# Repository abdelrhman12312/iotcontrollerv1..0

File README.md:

# iotcontrollerv1..0
I made a esp8266 controller board that can control up to 
16 relays with the MCP23017 with kicad

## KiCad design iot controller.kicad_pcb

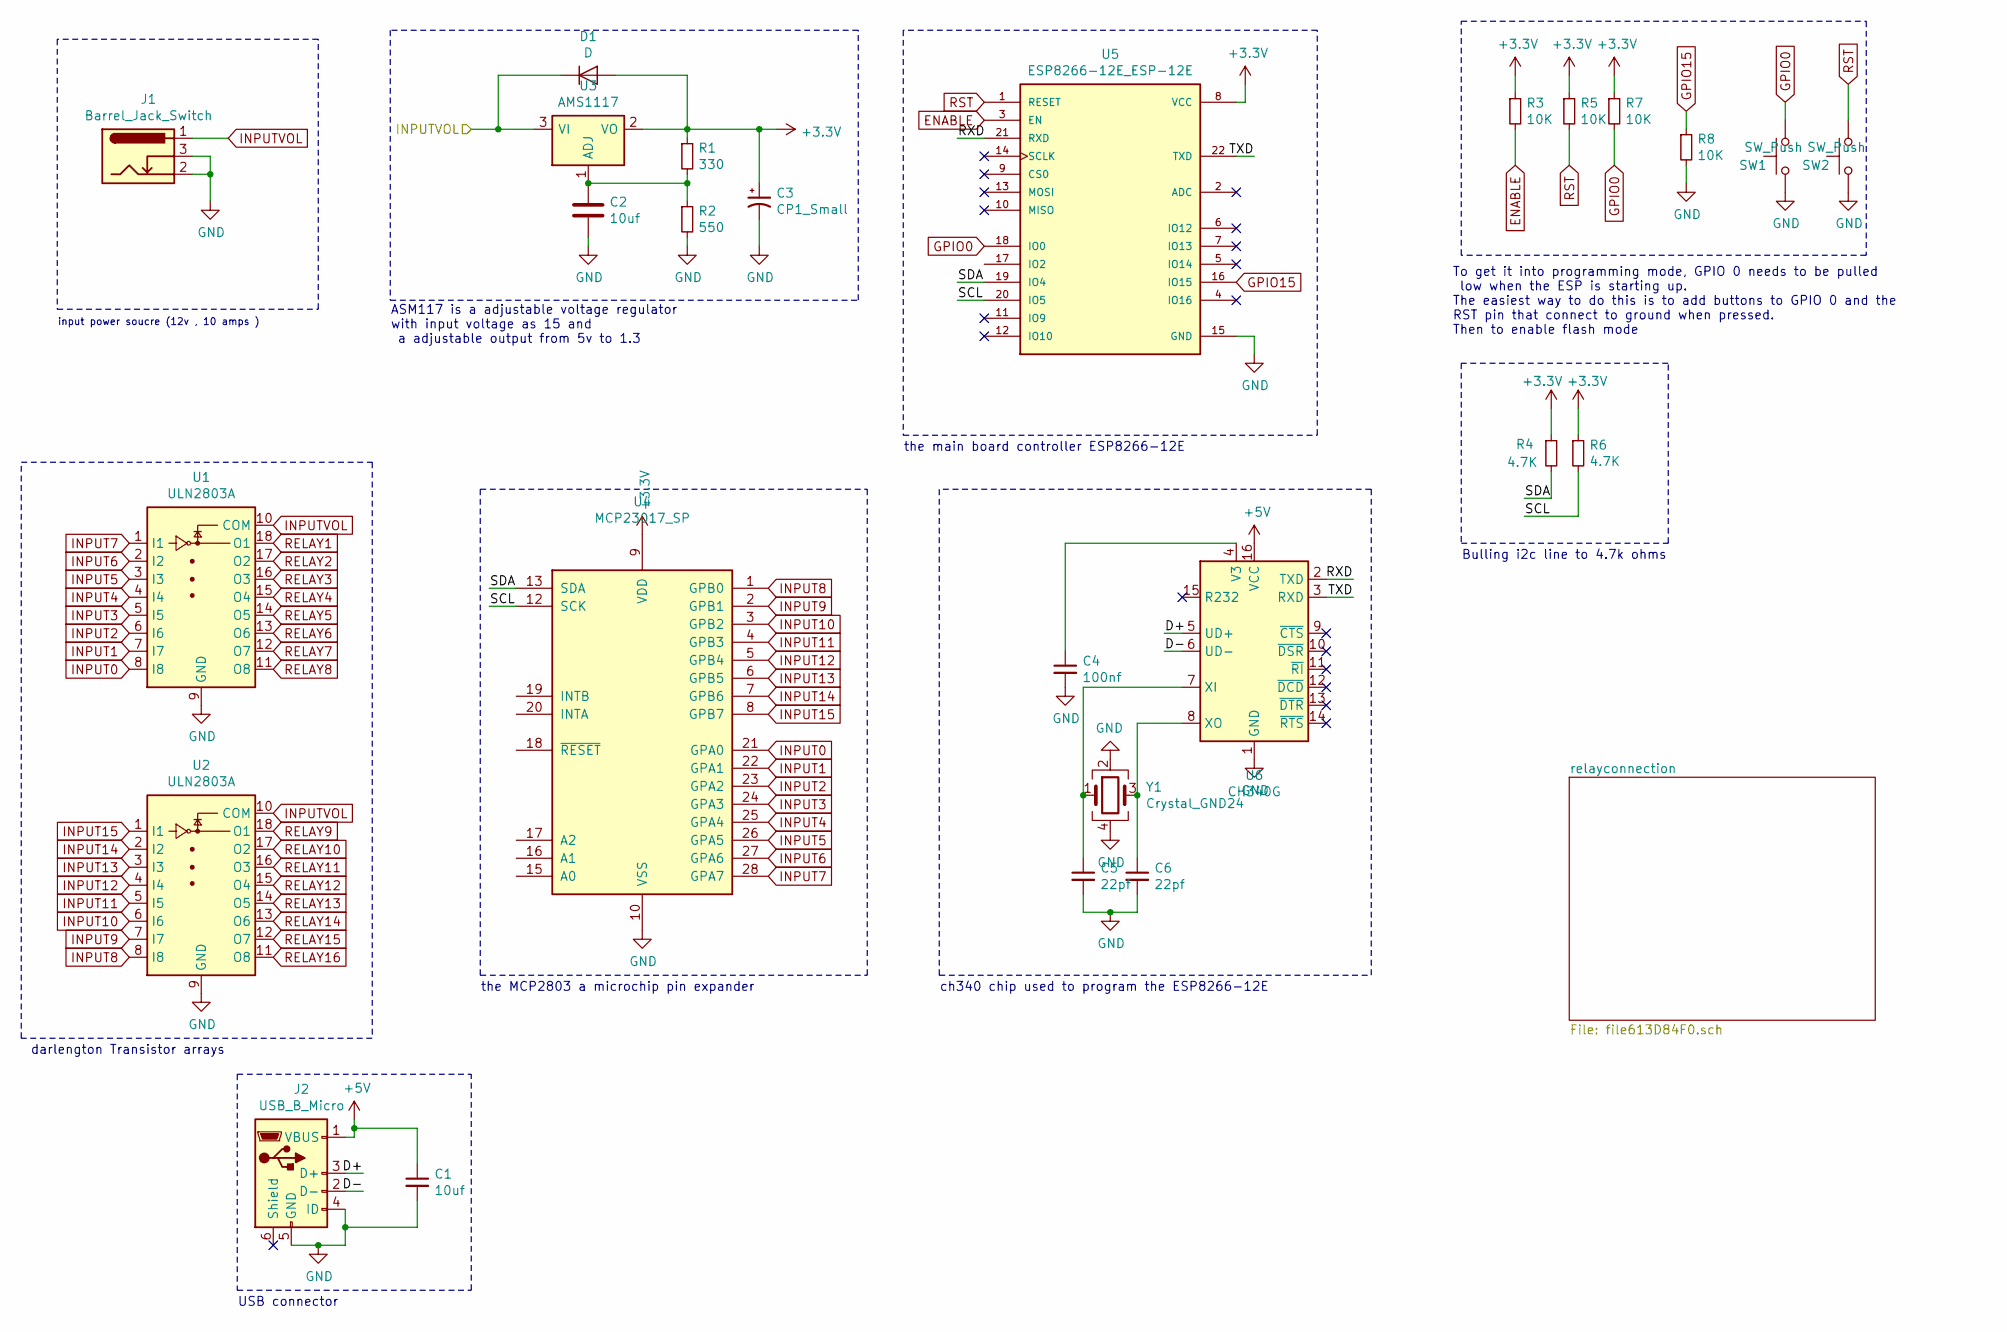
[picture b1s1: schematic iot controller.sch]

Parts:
C1, C2: 10uf; C_0603_1608Metric_Pad1.05x0.95mm_HandSolder
C3: CP1_Small; CP_Radial_D18.0mm_P7.50mm
C4: 100nf; C_0805_2012Metric_Pad1.15x1.40mm_HandSolder
C5, C6: 22pf; C_0805_2012Metric_Pad1.15x1.40mm_HandSolder
D1: D; D_SOD-123
J1: Barrel_Jack_Switch; BarrelJack_Horizontal
J2: USB_B_Micro; USB_Micro-B_GCT_USB3076-30-A
R1: 330; R_0805_2012Metric_Pad1.15x1.40mm_HandSolder
R2: 550; R_0805_2012Metric_Pad1.15x1.40mm_HandSolder
R3, R5, R7, R8: 10K; R_0805_2012Metric_Pad1.15x1.40mm_HandSolder
R4, R6: 4.7K; R_0805_2012Metric_Pad1.15x1.40mm_HandSolder
SW1, SW2: SW_Push; SW_Push_SPST_NO_Alps_SKRK
U1, U2: ULN2803A; DIP-18_W7.62mm
U3: AMS1117; SOT-223-3_TabPin2
U4: MCP23017_SP; DIP-28_W7.62mm
U5: ESP8266-12E_ESP-12E; ESP-12E
U6: CH340G; SOIC-16_3.9x9.9mm_P1.27mm
Y1: Crystal_GND24; Crystal_SMD_SeikoEpson_FA238V-4Pin_3.2x2.5mm

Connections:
+3V3: C3.1, D1.2 (A), R1.1, R3.1, R4.1, R5.1, R6.1, R7.1, U3.2 (VO), U4.9 (VDD), U5.8 (VCC)
+5V: C1.1, J2.1 (VBUS), U6.16 (VCC)
/D+: J2.3 (D+), U6.5 (UD+)
/D-: J2.2 (D-), U6.6 (UD-)
/RXD: U5.21 (RXD), U6.2 (TXD)
/SCL: R6.2, U4.12 (SCK), U5.20 (IO5)
/SDA: R4.2, U4.13 (SDA), U5.19 (IO4)
/TXD: U5.22 (TXD), U6.3 (RXD)
ENABLE: R3.2, U5.3 (EN)
GND: C1.2, C2.2, C3.2, C4.2, C5.2, C6.2, J1.2, J1.3, J2.4 (ID), J2.5 (GND), R2.2, R8.2, SW1.1, SW2.1, U1.9 (GND), U2.9 (GND), U4.10 (VSS), U5.15 (GND), U6.1 (GND), Y1.2, Y1.4
GPIO0: R7.2, SW1.2, U5.18 (IO0)
GPIO15: R8.1, U5.16 (IO15)
INPUT0: U1.8 (I8), U4.21 (GPA0)
INPUT1: U1.7 (I7), U4.22 (GPA1)
INPUT2: U1.6 (I6), U4.23 (GPA2)
INPUT3: U1.5 (I5), U4.24 (GPA3)
INPUT4: U1.4 (I4), U4.25 (GPA4)
INPUT5: U1.3 (I3), U4.26 (GPA5)
INPUT6: U1.2 (I2), U4.27 (GPA6)
INPUT7: U1.1 (I1), U4.28 (GPA7)
INPUT8: U2.8 (I8), U4.1 (GPB0)
INPUT9: U2.7 (I7), U4.2 (GPB1)
INPUT10: U2.6 (I6), U4.3 (GPB2)
INPUT11: U2.5 (I5), U4.4 (GPB3)
INPUT12: U2.4 (I4), U4.5 (GPB4)
INPUT13: U2.3 (I3), U4.6 (GPB5)
INPUT14: U2.2 (I2), U4.7 (GPB6)
INPUT15: U2.1 (I1), U4.8 (GPB7)
INPUTVOL: D1.1 (K), J1.1, U1.10 (COM), U2.10 (COM), U3.3 (VI); also elsewhere on the board
unnamed: C2.1, R1.2, R2.1, U3.1 (ADJ)
unnamed: C4.1, U6.4 (V3)
unnamed: C5.1, U6.7 (XI), Y1.1
unnamed: C6.1, U6.8 (XO), Y1.3
RELAY1: U1.18 (O1); also elsewhere on the board
RELAY2: U1.17 (O2); also elsewhere on the board
RELAY3: U1.16 (O3); also elsewhere on the board
RELAY4: U1.15 (O4); also elsewhere on the board
RELAY5: U1.14 (O5); also elsewhere on the board
RELAY6: U1.13 (O6); also elsewhere on the board
RELAY7: U1.12 (O7); also elsewhere on the board
RELAY8: U1.11 (O8); also elsewhere on the board
RELAY9: U2.18 (O1); also elsewhere on the board
RELAY10: U2.17 (O2); also elsewhere on the board
RELAY11: U2.16 (O3); also elsewhere on the board
RELAY12: U2.15 (O4); also elsewhere on the board
RELAY13: U2.14 (O5); also elsewhere on the board
RELAY14: U2.13 (O6); also elsewhere on the board
RELAY15: U2.12 (O7); also elsewhere on the board
RELAY16: U2.11 (O8); also elsewhere on the board
RST: R5.2, SW2.2, U5.1 (RESET)

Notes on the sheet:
To get it into programming mode, GPIO 0 needs to be pulled low when the ESP is starting up. The easiest way to do this is to add buttons to GPIO 0 and the RST pin that connect to ground when pressed. Then to enable flash mode
Bulling i2c line to 4.7k ohms
input power soucre (12v , 10 amps )
ASM117 is a adjustable voltage regulator with input voltage as 15 and a adjustable output from 5v to 1.3
the main board controller ESP8266-12E
the MCP2803 a microchip pin expander
darlengton Transistor arrays
USB connector
ch340 chip used to program the ESP8266-12E

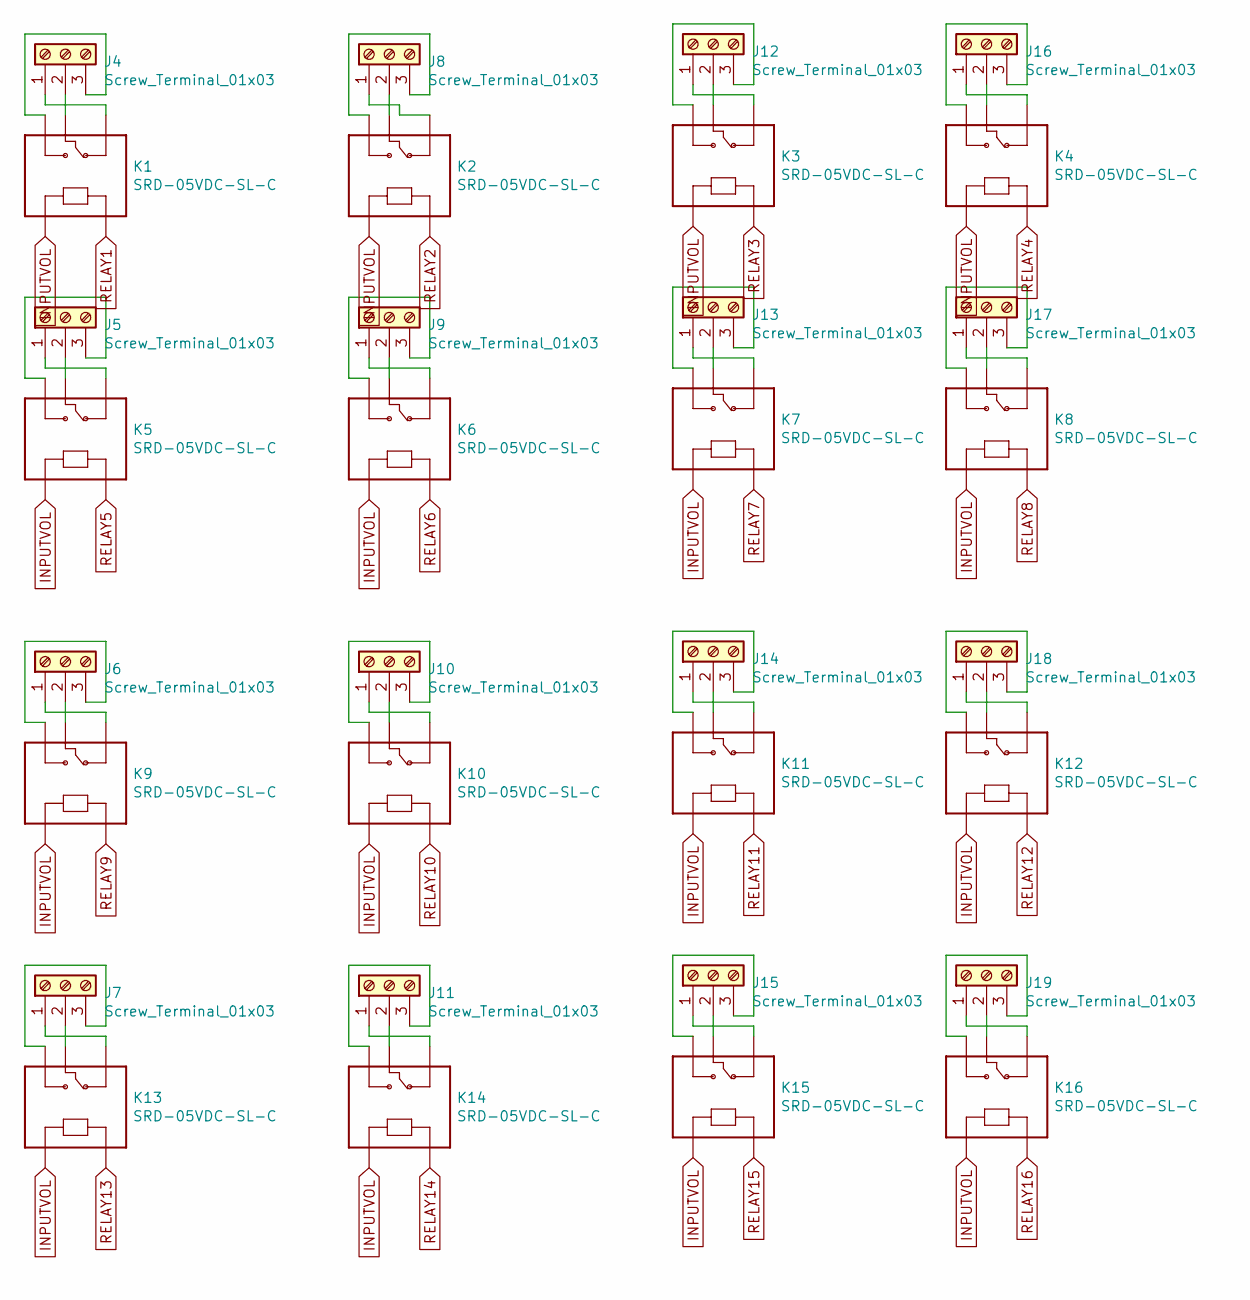
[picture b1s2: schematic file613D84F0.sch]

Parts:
J4, J5, J6, J7, J8, J9, J10, J11, J12, J13, J14, J15, J16, J17, J18, J19: Screw_Terminal_01x03; TerminalBlock_4Ucon_1x03_P3.50mm_Vertical
K1, K2, K3, K4, K5, K6, K7, K8, K9, K10, K11, K12, K13, K14, K15, K16: SRD-05VDC-SL-C; RELAY_SRD-05VDC-SL-C

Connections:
INPUTVOL: K1.A1, K2.A1, K3.A1, K4.A1, K5.A1, K6.A1, K7.A1, K8.A1, K9.A1, K10.A1, K11.A1, K12.A1, K13.A1, K14.A1, K15.A1, K16.A1; also elsewhere on the board
unnamed: J4.1, K1.NC
unnamed: J4.2, K1.COM
unnamed: J4.3, K1.NO
unnamed: J5.1, K5.NC
unnamed: J5.2, K5.COM
unnamed: J5.3, K5.NO
unnamed: J6.1, K9.NC
unnamed: J6.2, K9.COM
unnamed: J6.3, K9.NO
unnamed: J7.1, K13.NC
unnamed: J7.2, K13.COM
unnamed: J7.3, K13.NO
unnamed: J8.1, K2.NC
unnamed: J8.2, K2.COM
unnamed: J8.3, K2.NO
unnamed: J9.1, K6.NC
unnamed: J9.2, K6.COM
unnamed: J9.3, K6.NO
unnamed: J10.1, K10.NC
unnamed: J10.2, K10.COM
unnamed: J10.3, K10.NO
unnamed: J11.1, K14.NC
unnamed: J11.2, K14.COM
unnamed: J11.3, K14.NO
unnamed: J12.1, K3.NC
unnamed: J12.2, K3.COM
unnamed: J12.3, K3.NO
unnamed: J13.1, K7.NC
unnamed: J13.2, K7.COM
unnamed: J13.3, K7.NO
unnamed: J14.1, K11.NC
unnamed: J14.2, K11.COM
unnamed: J14.3, K11.NO
unnamed: J15.1, K15.NC
unnamed: J15.2, K15.COM
unnamed: J15.3, K15.NO
unnamed: J16.1, K4.NC
unnamed: J16.2, K4.COM
unnamed: J16.3, K4.NO
unnamed: J17.1, K8.NC
unnamed: J17.2, K8.COM
unnamed: J17.3, K8.NO
unnamed: J18.1, K12.NC
unnamed: J18.2, K12.COM
unnamed: J18.3, K12.NO
unnamed: J19.1, K16.NC
unnamed: J19.2, K16.COM
unnamed: J19.3, K16.NO
RELAY1: K1.A2; also elsewhere on the board
RELAY2: K2.A2; also elsewhere on the board
RELAY3: K3.A2; also elsewhere on the board
RELAY4: K4.A2; also elsewhere on the board
RELAY5: K5.A2; also elsewhere on the board
RELAY6: K6.A2; also elsewhere on the board
RELAY7: K7.A2; also elsewhere on the board
RELAY8: K8.A2; also elsewhere on the board
RELAY9: K9.A2; also elsewhere on the board
RELAY10: K10.A2; also elsewhere on the board
RELAY11: K11.A2; also elsewhere on the board
RELAY12: K12.A2; also elsewhere on the board
RELAY13: K13.A2; also elsewhere on the board
RELAY14: K14.A2; also elsewhere on the board
RELAY15: K15.A2; also elsewhere on the board
RELAY16: K16.A2; also elsewhere on the board

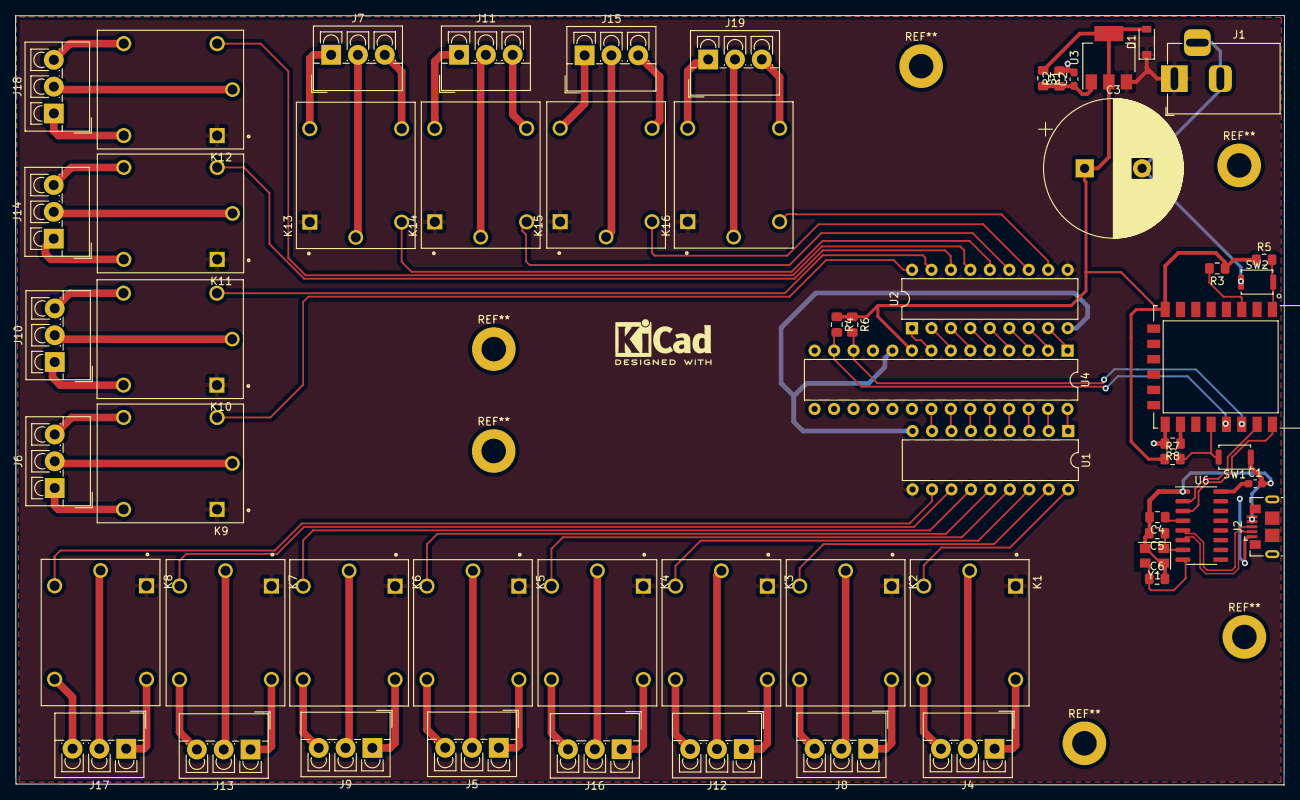
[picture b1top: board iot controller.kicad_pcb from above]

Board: 2 copper layers, 165.7 x 100.4 mm, 58 parts (0 on the bottom side), 98 nets.

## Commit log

2021-09-17 add USB3075-30-A.zip
